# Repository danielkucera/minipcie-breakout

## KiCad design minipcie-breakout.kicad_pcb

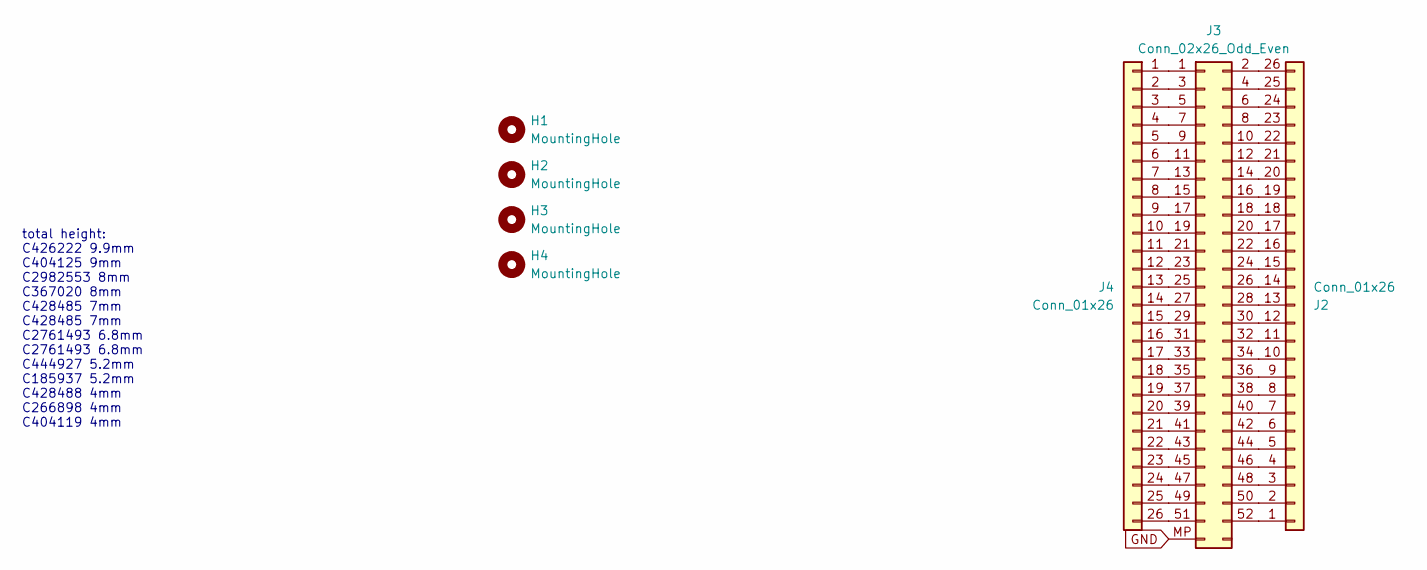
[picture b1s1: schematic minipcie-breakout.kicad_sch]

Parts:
H1, H2: MountingHole; MountingHole_2mm; LCSC C2915629
H3, H4: MountingHole; MountingHole_2mm
J2, J4: Conn_01x26; PinHeader_2x13_P2.54mm_Vertical
J3: Conn_02x26_Odd_Even; BUS_PCI_Express_Mini_Dual-small-pad; LCSC C404119

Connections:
GND: J3.MP (Pin_53)
unnamed: J2.1, J3.52
unnamed: J2.2, J3.50
unnamed: J2.3, J3.48
unnamed: J2.4, J3.46
unnamed: J2.5, J3.44
unnamed: J2.6, J3.42
unnamed: J2.7, J3.40
unnamed: J2.8, J3.38
unnamed: J2.9, J3.36
unnamed: J2.10, J3.34
unnamed: J2.11, J3.32
unnamed: J2.12, J3.30
unnamed: J2.13, J3.28
unnamed: J2.14, J3.26
unnamed: J2.15, J3.24
unnamed: J2.16, J3.22
unnamed: J2.17, J3.20
unnamed: J2.18, J3.18
unnamed: J2.19, J3.16
unnamed: J2.20, J3.14
unnamed: J2.21, J3.12
unnamed: J2.22, J3.10
unnamed: J2.23, J3.8
unnamed: J2.24, J3.6
unnamed: J2.25, J3.4
unnamed: J2.26, J3.2
unnamed: J3.1, J4.1
unnamed: J3.3, J4.2
unnamed: J3.5, J4.3
unnamed: J3.7, J4.4
unnamed: J3.9, J4.5
unnamed: J3.11, J4.6
unnamed: J3.13, J4.7
unnamed: J3.15, J4.8
unnamed: J3.17, J4.9
unnamed: J3.19, J4.10
unnamed: J3.21, J4.11
unnamed: J3.23, J4.12
unnamed: J3.25, J4.13
unnamed: J3.27, J4.14
unnamed: J3.29, J4.15
unnamed: J3.31, J4.16
unnamed: J3.33, J4.17
unnamed: J3.35, J4.18
unnamed: J3.37, J4.19
unnamed: J3.39, J4.20
unnamed: J3.41, J4.21
unnamed: J3.43, J4.22
unnamed: J3.45, J4.23
unnamed: J3.47, J4.24
unnamed: J3.49, J4.25
unnamed: J3.51, J4.26

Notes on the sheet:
total height: C426222 9.9mm C404125 9mm C2982553 8mm C367020 8mm C428485 7mm C428485 7mm C2761493 6.8mm C2761493 6.8mm C444927 5.2mm C185937 5.2mm C428488 4mm C266898 4mm C404119 4mm

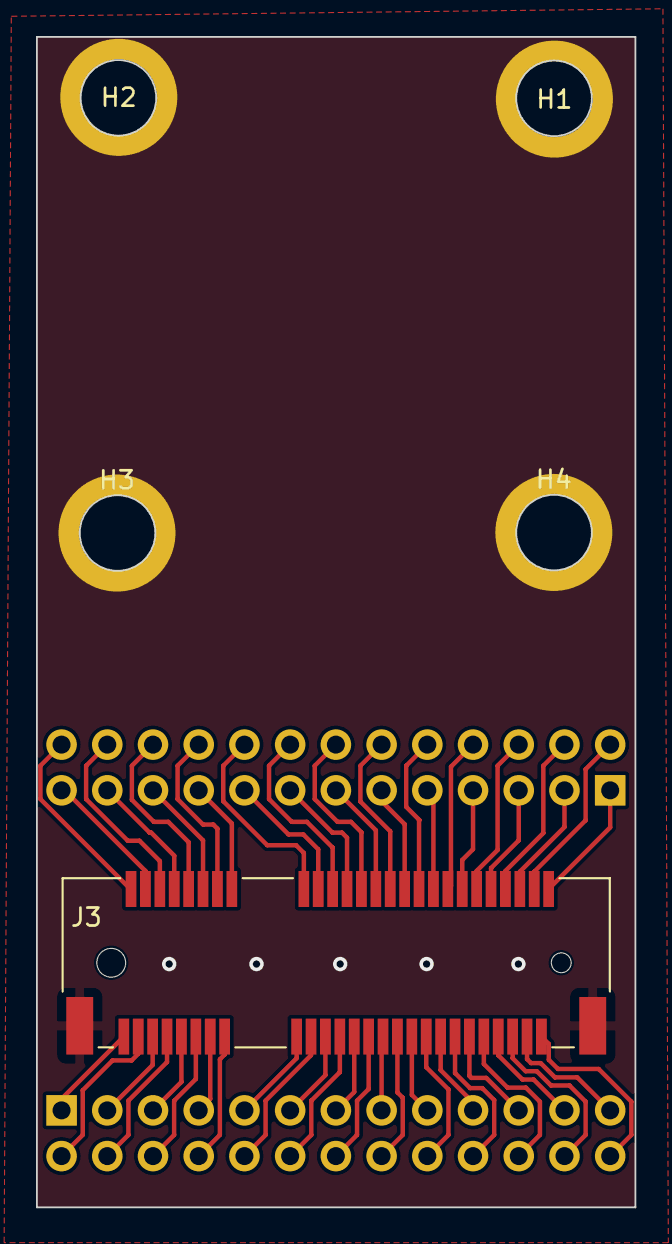
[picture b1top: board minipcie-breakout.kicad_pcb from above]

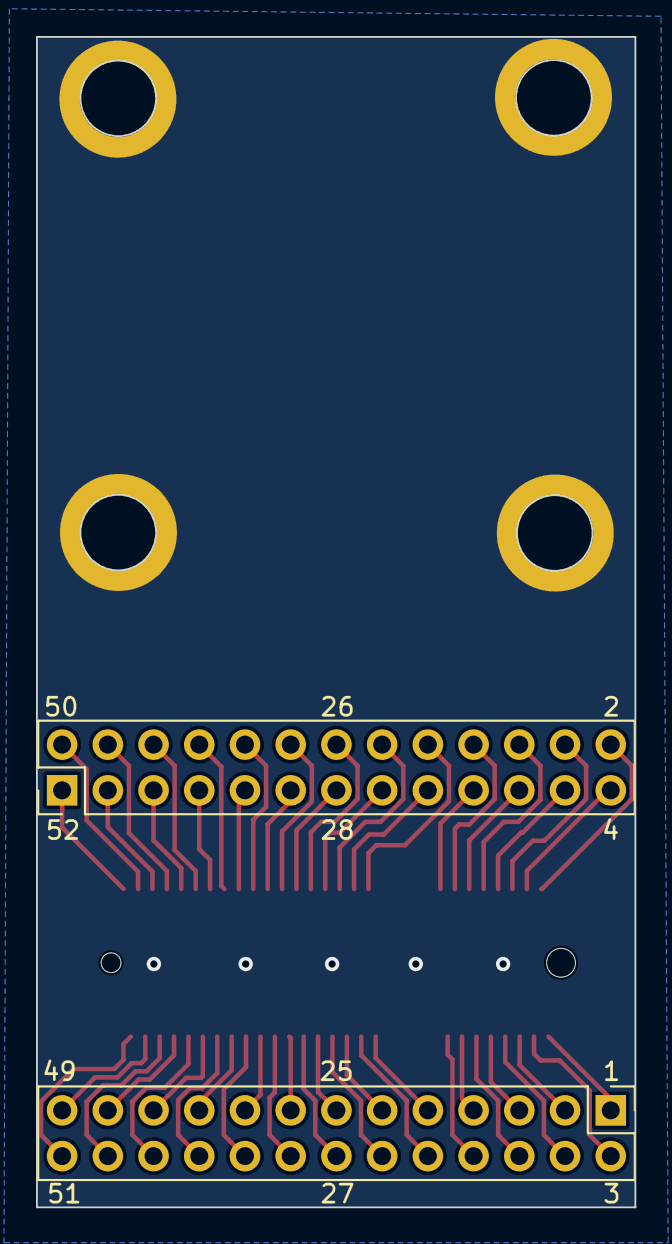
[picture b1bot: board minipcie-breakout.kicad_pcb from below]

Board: 2 copper layers, 33.3 x 65.0 mm, 7 parts (2 on the bottom side), 52 nets.

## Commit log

2025-06-20 initial commit, version for elecrow sales
2026-05-15 latest version
